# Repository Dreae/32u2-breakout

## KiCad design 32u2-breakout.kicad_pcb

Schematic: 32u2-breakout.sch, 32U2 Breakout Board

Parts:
C1, C2: 22 pF; C_0402_1005Metric
C3: 10uF; C_1210_3225Metric
C4: 1uF; C_0805_2012Metric
D1: LED; LED_0805_2012Metric
J1, J2: Conn_01x08_Female; PinHeader_1x08_P2.54mm_Vertical
J3: Conn_01x04_Female; PinHeader_1x04_P2.54mm_Vertical
J4: USB_B_Micro; USB_Micro-B_Molex-105017-0001
J5: Conn_02x03_Counter_Clockwise; PinHeader_2x03_P2.54mm_Vertical
R1, R2: 22; R_0402_1005Metric
R3: 200; R_0402_1005Metric
R4: 10k; R_0402_1005Metric
SW1: SW_DIP_x01; SW_SPST_TL3305A
U1: ATmega32U2-AU; TQFP-32_7x7mm_P0.8mm
Y1: 16 MHz; Crystal_SMD_SeikoEpson_TSX3225-4Pin_3.2x2.5mm

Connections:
GND: C1.2, C2.2, C3.2, C4.2, J4.5, J5.4, R3.2, SW1.2, U1.3 (GND), U1.28 (UGND)
unnamed: C1.1, U1.2 (PC0/XTAL2), Y1.3
unnamed: C2.1, U1.1 (XTAL1), Y1.1
unnamed: C4.1, U1.27 (UCAP)
unnamed: D1.1, R3.1
unnamed: D1.2, U1.22 (PC7)
unnamed: J1.1, U1.14 (PB0)
unnamed: J1.2, J5.2, U1.15 (PB1)
unnamed: J1.3, J5.5, U1.16 (PB2)
unnamed: J1.4, J5.1, U1.17 (PB3)
unnamed: J1.5, U1.18 (PB4)
unnamed: J1.6, U1.19 (PB5)
unnamed: J1.7, U1.20 (PB6)
unnamed: J1.8, U1.21 (PB7)
unnamed: J2.1, U1.6 (PD0)
unnamed: J2.2, U1.7 (PD1)
unnamed: J2.3, U1.8 (PD2)
unnamed: J2.4, U1.9 (PD3)
unnamed: J2.5, U1.10 (PD4)
unnamed: J2.6, U1.11 (PD5)
unnamed: J2.7, U1.12 (PD6)
unnamed: J2.8, U1.13 (~HWB~/PD7)
unnamed: J3.1, U1.5 (PC2)
unnamed: J3.2, U1.26 (PC4)
unnamed: J3.3, U1.25 (PC5)
unnamed: J3.4, U1.23 (PC6)
unnamed: J4.2, R2.2
unnamed: J4.3, R1.2
unnamed: J5.3, R4.2, SW1.1, U1.24 (PC1/~RESET)
unnamed: R1.1, U1.29 (D+)
unnamed: R2.1, U1.30 (D-)
VCC: C3.1, J4.1, J5.6, R4.1, U1.4 (VCC), U1.31 (UVCC), U1.32 (AVCC)

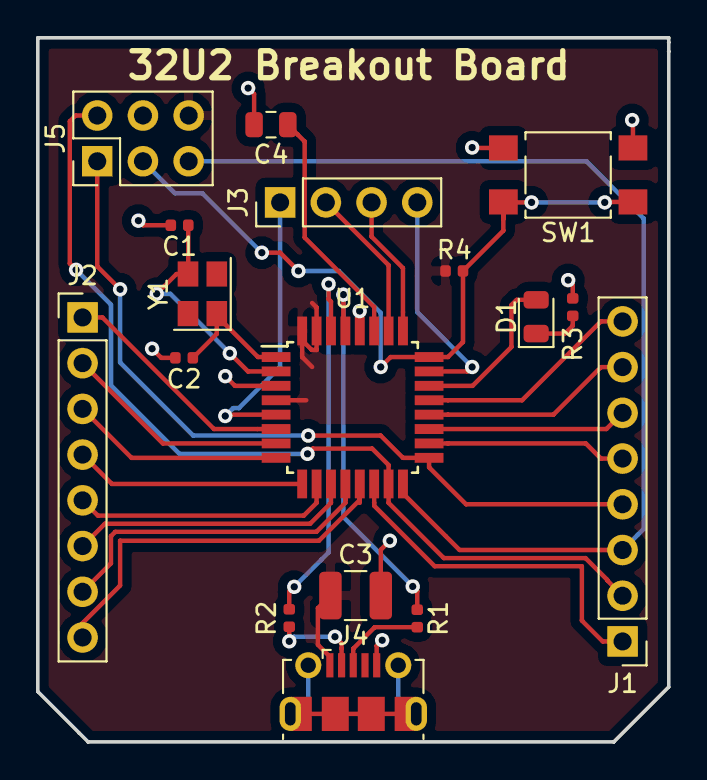
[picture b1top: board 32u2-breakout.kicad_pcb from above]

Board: 2 copper layers, 35.1 x 39.1 mm, 17 parts (0 on the bottom side), 32 nets.

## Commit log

2018-12-27 Initial
2019-01-09 Add SPI header, use different crystal
2019-01-09 Relocate ISP pin header
